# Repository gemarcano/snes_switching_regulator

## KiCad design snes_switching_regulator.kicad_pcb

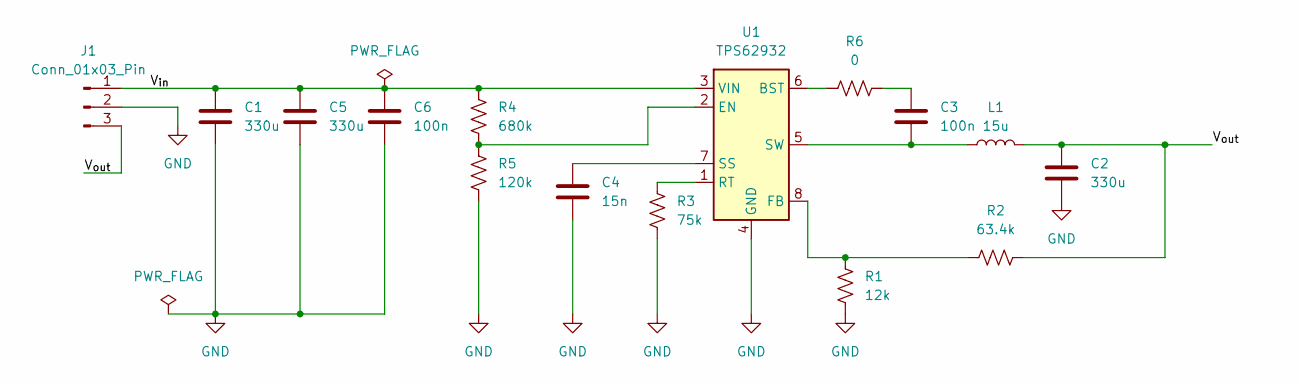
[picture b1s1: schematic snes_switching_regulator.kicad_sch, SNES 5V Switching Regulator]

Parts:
C1, C2, C5: 330u; CP_Radial_D6.3mm_P2.50mm; Digikey Part Number 399-A750EM337M1CAAE015-ND
C3, C6: 100n; C_0603_1608Metric_Pad1.08x0.95mm_HandSolder; Digikey Part Number 1276-1935-1-ND
C4: 15n; C_0603_1608Metric_Pad1.08x0.95mm_HandSolder; Digikey Part Number 399-C0603C153M3GEC7411CT-ND
J1: Conn_01x03_Pin; PinHeader_1x03_P2.54mm_Vertical; Digikey Part Number S1112EC-03-ND
L1: 15u; BFSI00121109150M05; Digikey Part Number 553-BFSI00121109150M05CT-ND
R1: 12k; R_0603_1608Metric_Pad0.98x0.95mm_HandSolder; Digikey Part Number 118-CR0603-FX-1202ELFCT-ND
R2: 63.4k; R_0603_1608Metric_Pad0.98x0.95mm_HandSolder; Digikey Part Number RMCF0603FT63K4CT-ND
R3: 75k; R_0603_1608Metric_Pad0.98x0.95mm_HandSolder; Digikey Part Number YAG3629CT-ND
R4: 680k; R_0603_1608Metric_Pad0.98x0.95mm_HandSolder; Digikey Part Number CR0603-FX-6803ELFCT-ND
R5: 120k; R_0603_1608Metric_Pad0.98x0.95mm_HandSolder; Digikey Part Number CR0603-FX-1203ELFCT-ND
R6: 0; R_0603_1608Metric_Pad0.98x0.95mm_HandSolder; Digikey Part Number 1292-WR06X000PTLCT-ND
U1: TPS62932; SOT-583-8; Digikey Part Number 296-TPS62932DRLRCT-ND

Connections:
/V_{in}: C1.1, C5.1, C6.1, J1.1, R4.1, U1.3 (VIN)
/V_{out}: C2.1, J1.3, L1.2, R2.2
GND: C1.2, C2.2, C4.2, C5.2, C6.2, J1.2, R1.2, R3.2, R5.2, U1.4 (GND)
unnamed: C3.1, R6.2
unnamed: R6.1, U1.6 (BST)
unnamed: R4.2, R5.1, U1.2 (EN)
unnamed: R1.1, R2.1, U1.8 (FB)
unnamed: R3.1, U1.1 (RT)
unnamed: C4.1, U1.7 (SS)
unnamed: C3.2, L1.1, U1.5 (SW)

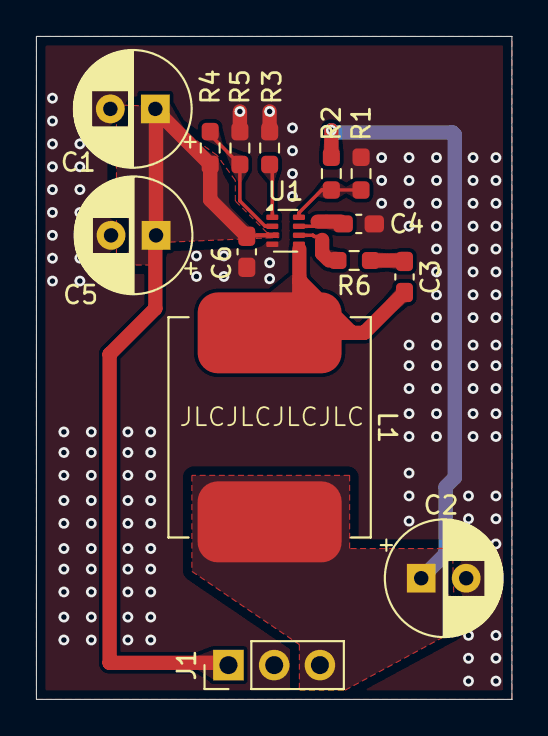
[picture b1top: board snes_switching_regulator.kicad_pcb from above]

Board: 2 copper layers, 26.4 x 36.8 mm, 15 parts (0 on the bottom side), 10 nets.

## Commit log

2024-11-27 Add Rev A manufacturing files
    - Exclude any zip files from the PCB folder
2024-11-27 Add Spice model, calculations for part selection
2024-11-27 Change Spice model path to relative
